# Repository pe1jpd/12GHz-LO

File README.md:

# 12GHz-LO
A simple 12GHz PLL based local oscillator.

See description and pictures at www.pe1jpd.nl.

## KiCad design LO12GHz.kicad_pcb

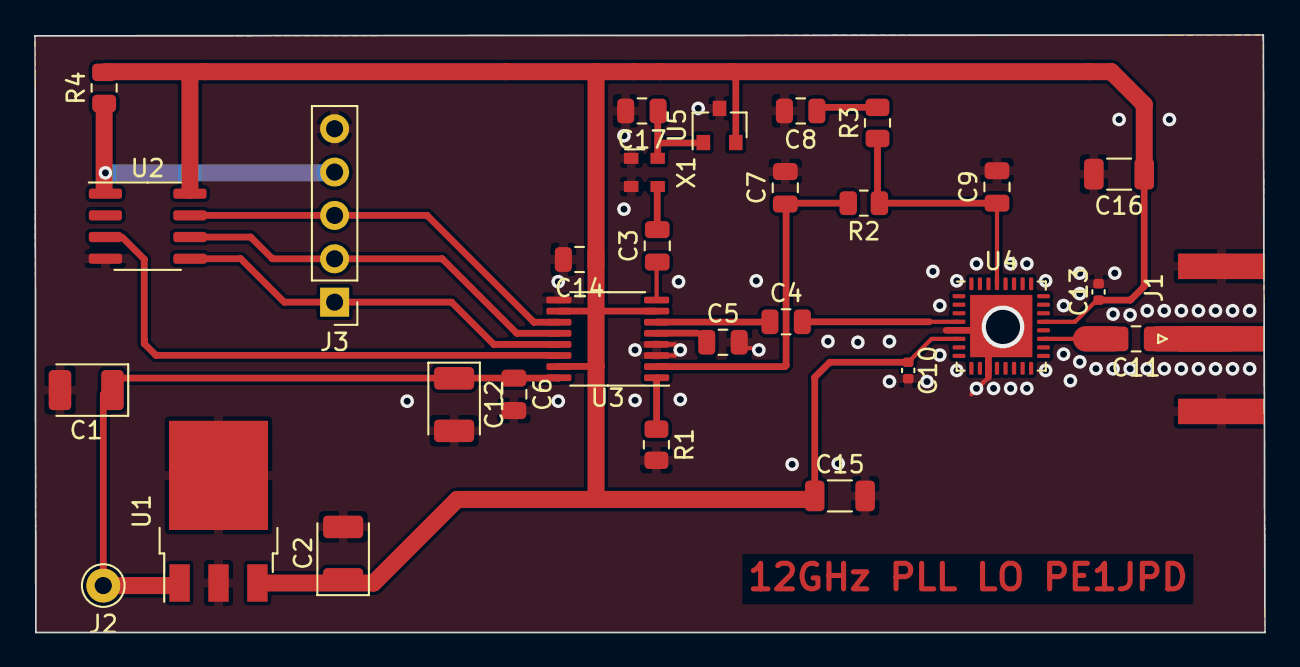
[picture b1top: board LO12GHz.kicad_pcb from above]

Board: 2 copper layers, 72.0 x 35.0 mm, 30 parts (0 on the bottom side), 19 nets.

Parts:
C1, C2, C12: CP; CP_EIA-3528-12_Kemet-T
C3, C4, C5, C6, C7, C8, C9, C11, C14, C17: C; C_0805_2012Metric
C10, C13: C; C_0402_1005Metric
C15, C16: C; C_1206_3216Metric
J1: SMA; SMA_Amphenol_132289_EdgeMount
J2: Conn_01x01; Pin_D1.0mm_L10.0mm
J3: Conn_01x05_Male; PinHeader_1x05_P2.54mm_Vertical
R1, R2, R3, R4: R; R_0805_2012Metric
U1: L78L05_SO8; TO-252-3_TabPin2
U2: ATtiny13-20SSU; SOIC-8_3.9x4.9mm_P1.27mm
U3: ADF4113HVBRUZ; TSSOP-16_4.4x5mm_P0.65mm
U4: HMC515; QFN-32-1EP_5x5mm_P0.5mm_EP3.65x3.65mm
U5: LM3480-3.3; SOT-23
X1: ASTX-13-C-40.000MHZ-I05-T; Oscillator_SMD_Abracon_ASDMB-4Pin_2.5x2.0mm

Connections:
Earth: C1.2, C2.2, C5.2, C6.2, C7.2, C8.2, C9.2, C10.2, C12.2, C13.2, C14.2, C15.2, C16.2, C17.2, J1.2, J3.5, R1.2, U1.2, U2.4, U3.3, U3.4, U3.9, U4.5, U4.11, U5.3, X1.1, X1.2
unnamed: C1.1, C6.1, C12.1, J2.1, U1.1, U3.16
unnamed: C3.1, U3.8
unnamed: C3.2, X1.3
unnamed: C4.1, U3.6
unnamed: C4.2, U4.4
unnamed: C5.1, U3.5
unnamed: C7.1, R2.2, U3.2
unnamed: C8.1, R3.2
unnamed: C9.1, R2.1, R3.1, U4.29
unnamed: C2.1, C10.1, C13.1, C14.1, C15.1, C16.1, R4.2, U1.3, U2.8, U3.7, U3.10, U3.15, U4.6, U4.21, U5.2
unnamed: C11.1, J1.1
unnamed: C11.2, U4.19
unnamed: C17.1, U5.1, X1.4
unnamed: J3.1, U2.5, U3.13
unnamed: J3.2, U2.6, U3.12
unnamed: J3.3, U2.7, U3.11
unnamed: J3.4, R4.1, U2.1
unnamed: R1.1, U3.1

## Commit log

2020-12-25 12GHzLO.c
